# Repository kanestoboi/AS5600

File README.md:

# AS5600

Arduino library for the AS5600 12-bit Magnetic Encoder. This library was written for the [NEMA-17 AS5600 Board](https://github.com/kanestoboi/AS5600-Nema-17-Board).

Features
* Read 12 bit value (0-4095)
* Read angle value in degrees (0-360 degrees)
* Get magnetic strength 
* Get gain

## Example 
The following example reads the angle (0-360) of the magnet relative to the AS5600 encoder in increments of 360/4095
```c
#include <AS5600.h>

AS5600 encoder;
float output;

void setup() {
  Serial.begin(9600);
}

void loop() {
  // get the angle in degrees of the encoder
  output = encoder.getAngle();
  Serial.println(output);
}
````

## More Examples
See [`examples`](https://github.com/kanestoboi/AS5600/tree/master/examples) directory in this repository for more examples including continuous rotation.

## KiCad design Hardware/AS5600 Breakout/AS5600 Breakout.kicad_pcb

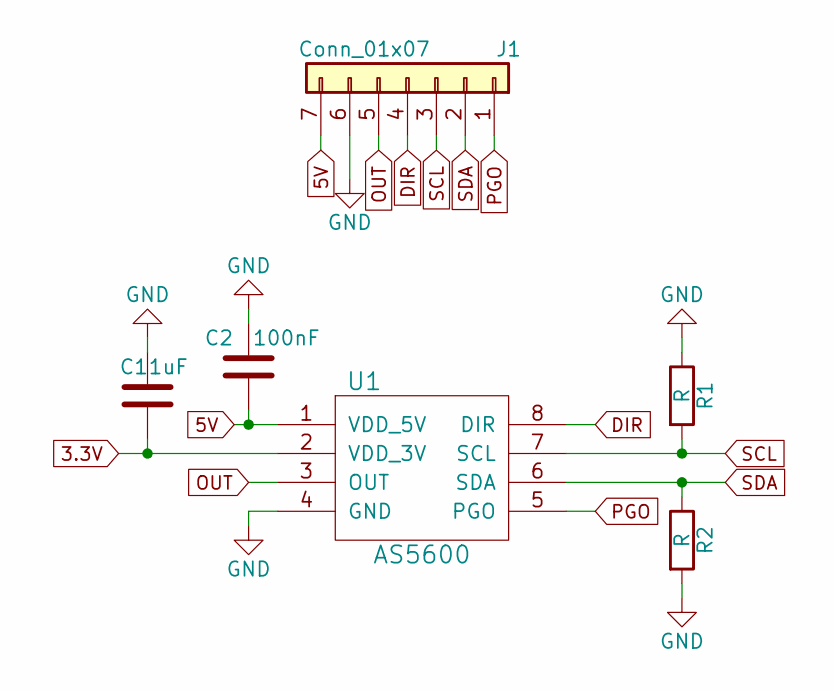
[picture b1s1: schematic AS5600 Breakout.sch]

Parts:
C1: 1uF; C_0805
C2: 100nF; C_0805
J1: Conn_01x07; Pin_Header_Angled_1x07_Pitch2.54mm
R1, R2: R; R_0805
U1: AS5600; SOIC-8-N

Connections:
3.3V: C1.2, U1.2 (VDD_3V)
5V: C2.1, J1.7, U1.1 (VDD_5V)
DIR: J1.4, U1.8 (DIR)
GND: C1.1, C2.2, J1.6, R1.1, R2.2, U1.4 (GND)
OUT: J1.5, U1.3 (OUT)
PGO: J1.1, U1.5 (PGO)
SCL: J1.3, R1.2, U1.7 (SCL)
SDA: J1.2, R2.1, U1.6 (SDA)

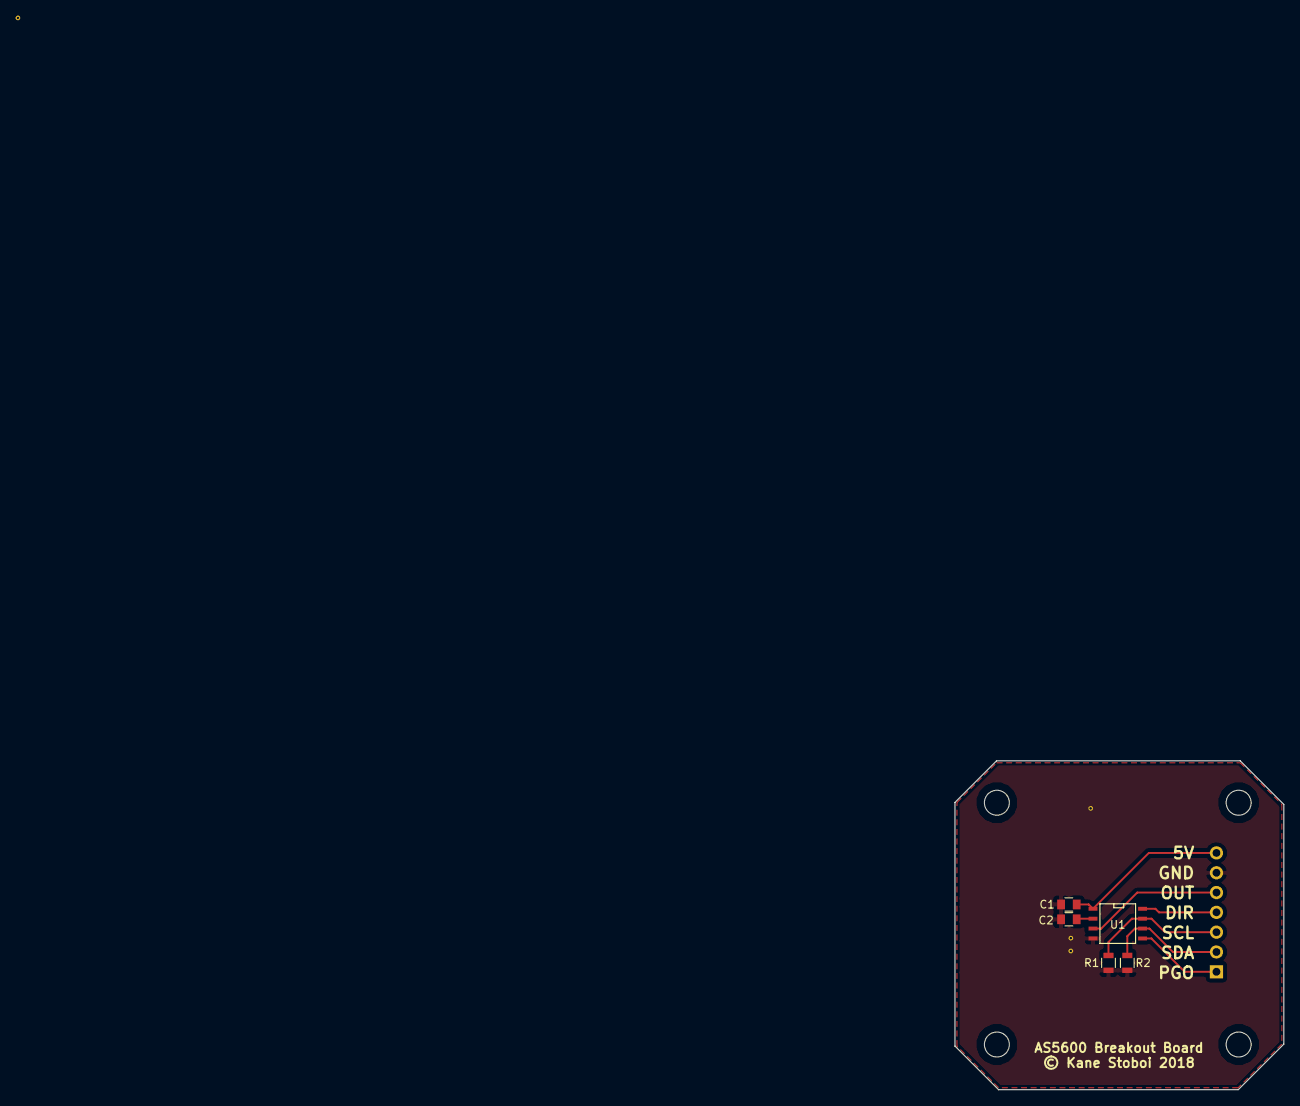
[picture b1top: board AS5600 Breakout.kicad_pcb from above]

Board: 2 copper layers, 42.2 x 42.2 mm, 6 parts (1 on the bottom side), 8 nets.

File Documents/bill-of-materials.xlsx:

ECTE451 Kane Stoboi
 |  |  |  |  |  |  |  |  |  |  | © 2012-2014 Vertex42 LLC
 |  |  |  |  |  | [42] |  |  |  |  | Bill of Materials Template
 | Part Count : | 175
 | Total Cost : | 239.79999999999998
Part # | Part Name | Supplier | Description | Supplier Part Number | Qty | Picture | Unit Cost | Shipping | Cost
 | TMC2100 Breakout | Digikey |  | 1460-1159-ND | 3 |  | 11.32 | 0 | 33.96
 | AS5600-ASOM | Digikey |  | AS5600-ASOMCT-ND | 5 |  | 5.66 |  | 28.3
 | Teensy 3.6 | Digikey |  | 1568-1465-ND | 2 |  | 51.78 |  | 103.56
 | 100nF Capacitor | Digikey |  | 1276-1007-1-ND | 20 |  | 6.4000000000000001E-2 |  | 1.28
 | 10uF Capacitor | Digikey |  | 1276-1096-1-ND | 20 |  | 0.16600000000000001 |  | 3.3200000000000003
 | LED_0603 | Digikey |  | 475-3118-1-ND | 10 |  | 0.437 |  | 4.37
 | Pin Header | Digikey |  | 732-5342-ND | 10 |  | 1.0469999999999999 |  | 10.469999999999999
 | 47k Resistor 0805 | Digikey |  | 311-47.0KCRCT-ND | 100 |  | 2.5600000000000001E-2 |  | 2.56
 | AEAT-6600-T16 | Mouser |  | 630-AEAT-6600-T16 | 3 |  | 11.38 |  | 34.14
 | Circuit Board Manufacture | Elecrow |  | - | 2 |  | 4.9000000000000004 | 8.0399999999999991 | 17.84
 |  |  |  |  |  |  |  |  | 0
 | Total |  |  |  | 175 |  |  |  | 239.79999999999998

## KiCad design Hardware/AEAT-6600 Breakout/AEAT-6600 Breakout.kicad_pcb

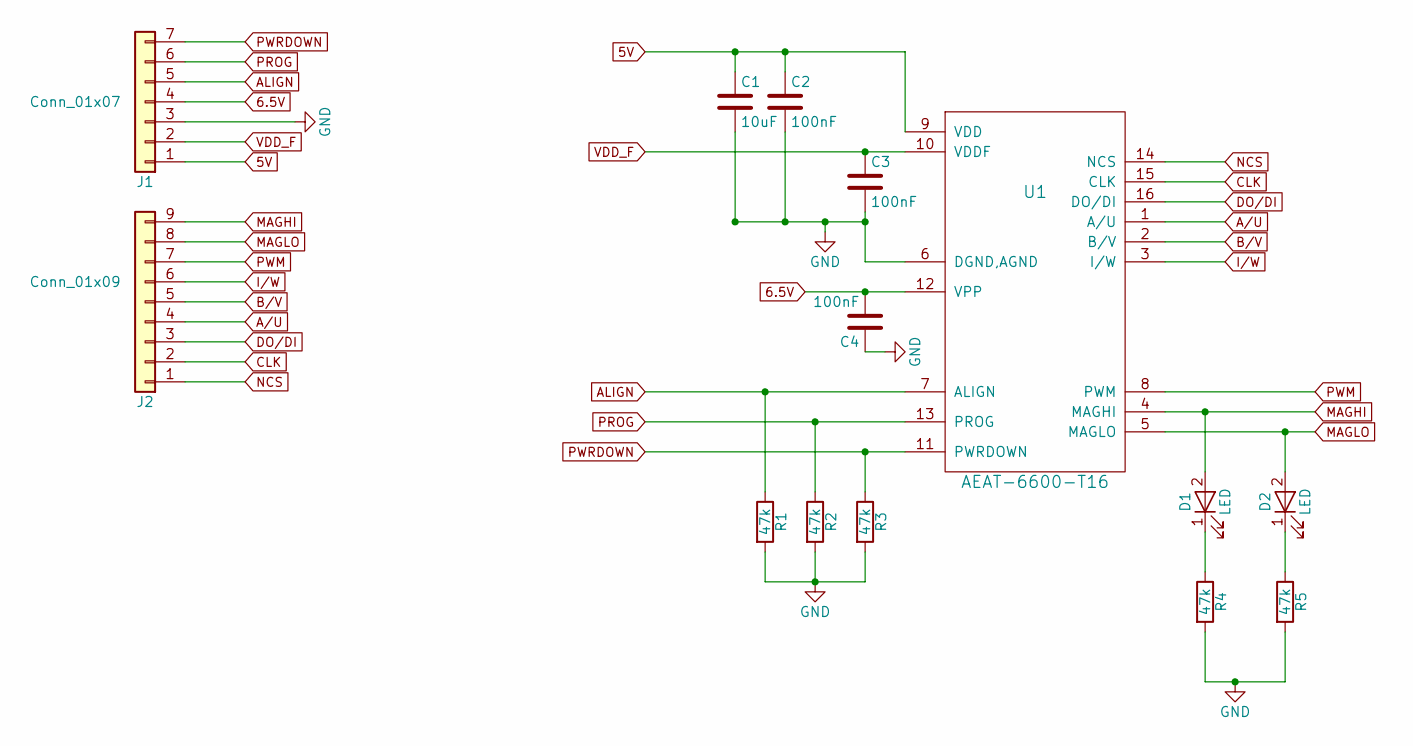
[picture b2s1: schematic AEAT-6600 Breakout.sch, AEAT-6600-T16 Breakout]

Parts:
C1: 10uF; C_0805
C2, C3, C4: 100nF; C_0805
D1, D2: LED; LED_0603
J1: Conn_01x07; Pin_Header_Angled_1x07_Pitch2.54mm
J2: Conn_01x09; Pin_Header_Angled_1x09_Pitch2.54mm
R1, R2, R3, R4, R5: 47k; R_0805
U1: AEAT-6600-T16; TSSOP-16_4.4x5mm_Pitch0.65mm

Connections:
5V: C1.1, C2.1, J1.1, U1.9 (VDD)
6.5V: C4.2, J1.4, U1.12 (VPP)
A/U: J2.4, U1.1 (A/U)
ALIGN: J1.5, R1.1, U1.7 (ALIGN)
B/V: J2.5, U1.2 (B/V)
CLK: J2.2, U1.15 (CLK)
DO/DI: J2.3, U1.16 (DO/DI)
GND: C1.2, C2.2, C3.2, C4.1, J1.3, R1.2, R2.2, R3.2, R4.2, R5.2, U1.6 (DGND,AGND)
I/W: J2.6, U1.3 (I/W)
MAGHI: D1.2 (A), J2.9, U1.4 (MAGHI)
MAGLO: D2.2 (A), J2.8, U1.5 (MAGLO)
NCS: J2.1, U1.14 (NCS)
unnamed: D1.1 (K), R4.1
unnamed: D2.1 (K), R5.1
PROG: J1.6, R2.1, U1.13 (PROG)
PWM: J2.7, U1.8 (PWM)
PWRDOWN: J1.7, R3.1, U1.11 (PWRDOWN)
VDD_F: C3.1, J1.2, U1.10 (VDDF)

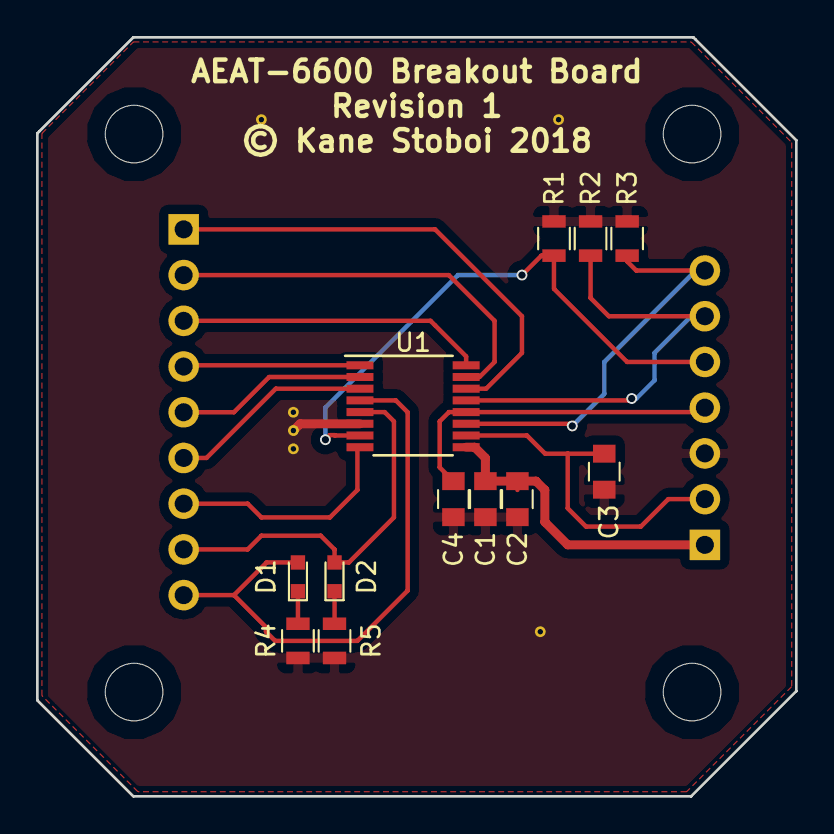
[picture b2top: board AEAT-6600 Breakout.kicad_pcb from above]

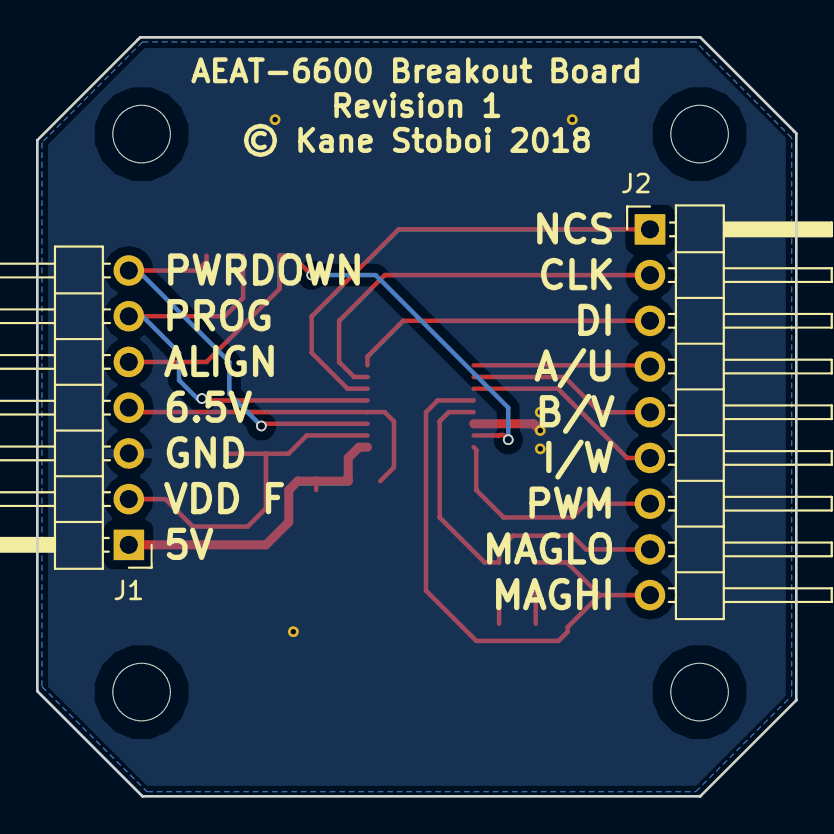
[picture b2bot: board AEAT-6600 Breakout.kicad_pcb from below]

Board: 2 copper layers, 42.2 x 42.2 mm, 14 parts (2 on the bottom side), 18 nets.

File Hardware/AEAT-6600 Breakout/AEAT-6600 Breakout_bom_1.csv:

Component,Description,Part,References,Value,Footprint,Quantity Per PCB,Datasheet,Supplier Part Number,Supplier,Cost Each
1,Unpolarized capacitor,C,C2 C3 C4,100nF,C_0805,3,,1276-1007-1-ND,Digikey,0.064
2,Unpolarized capacitor,C,C1,10uF,C_0805,1,,1276-1096-1-ND,Digikey,0.166
3,LED generic,LED,D1 D2,LED,LED_0603,2,,475-3118-1-ND,Digikey,0.437
4,"Generic connector, single row, 01x07",Conn_01x07,J1,Conn_01x07,Pin_Header_Angled_1x07_Pitch2.54mm,1,,732-5342-ND,Digikey,1.047
5,"Generic connector, single row, 01x09",Conn_01x09,J2,Conn_01x09,Pin_Header_Angled_1x09_Pitch2.54mm,1,,732-5342-ND,Digikey,1.047
6,Resistor,R,R1 R2 R3 R4 R5,47k,R_0805,5,,311-47.0KCRCT-ND,Digikey,0.056
7,,AEAT-6600-T16,U1,AEAT-6600-T16,TSSOP-16_4.4x5mm_Pitch0.65mm,1,,,,





Component Groups:,7
Component Count:,14
Fitted Components:,14
Number of PCBs:,1
Total components:,14
Schematic Version:,1
Schematic Date:,2018-08-18
BoM Date:,19/08/2018 10:19:32 AM
Schematic Source:,C:\Users\kanes\Documents\Projects\ECTE451\Hardware\AEAT-6600 Breakout\AEAT-6600 Breakout.sch
KiCad Version:,Eeschema 4.0.7

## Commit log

2018-08-01 initial commit of report, literature planner and project proposal form
2018-08-07 added brief overview to proposal
2018-08-08 made save
2018-08-08 - Added further to Brief Overview - Added further to Project Description - Added further to Project Plan - Added Further to Resources Required
    - Added TMC2100 Datasheet and application noted
    - Added forms to repo
    - Added endnote library
2018-08-08 added redline
2018-08-11 - added more journals, datasheets and application notes - added redline for project proposal form - added more references to endnote library
2018-08-13 Added more changes to proposal form added BOM Added more references
2018-08-18 Completed Project Proposal
2018-08-18 More journals added
2018-08-18 - Updated BOM - Created AS5600 Breakout schematic and board
2018-08-18 Completed schematic of AEAT-6600 Breakout
2018-08-18 Completed AEAT-6600 Breakout
2018-08-19 Completed breakout boards and BOM
2018-08-22 Created gerbers for pcbs
2018-08-22 Started developing AS5600 library
2018-09-20 - added further to AS5600 arduino library - created model for circuit board holder - finished MATLAB model for AS5600 feedback loop, ready for testing
2018-09-20 - updated filter for MATLAB model - Fixed bug in arduino code causing MSB to be read as LSB and vise versa
2018-09-23 - changed vco to PWM output - Moved encoder into subsystem in simulink model
2018-09-24 - added blank thesis word document
2018-09-24 - removed unnecessary info from abbreviations - removed change history table - added chapter titles
2018-09-26 - modified literature planner
2018-09-26 - added to report introduction and lit review - added reference to endnote
2018-09-29 started implementing contro system in arduino code
2018-09-30 - removed filter as capacitor has been added to 3.3V pin on breakout board - changed drive pin to be using ppm pin
2018-09-30 - added config pins for motor mode control
2018-10-01 - added more documents
2018-10-01 - added more journals to lit review
2018-10-02 - added functions to switch from stealth chop to spread cycle - moved encoder status code to function - moved error calc to function - added enable pin for motor driver - added frequency function to 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
2018-10-03 - added more to lit review
2018-10-03 - added more lit review notes
2018-10-03 - testing spread cycle power
2018-10-03 added more lit review stuff
2018-10-03 more lit review comments
2018-10-07 - added image of stepper motor diagram
2018-10-07 - updated stepper motor schematic
2018-10-07 - added timer interrupt for as5600
2018-10-10 changed read two registers to read one at a time
2018-10-10 moving AS5600 to separate repo
2018-10-10 - added keywords file - added AS5600.ino file - changed private variables and functions to have _ prefix
2018-10-10 updated keywords with function names
2018-10-10 moved example into examples folder
2018-10-10 changed example name to readAngle
2018-10-10 moved example to readAngle folder
2018-10-11 - moving AS5600 into separate repo
2018-10-11 - added basic data collected for position and velocity
2018-10-11 - added more position data for stealth and spreadcycle at 200Hz
2018-10-11 added image of AS5600 breakout board
2018-10-11 adding subtree
2018-10-11 adding readMagnet example
2019-02-09 added continuous rotation example code
2019-02-09 added functionality to readAngle example
2019-04-02 many bug fixes:
    * _getRegister2 broken, fixed with call to _getRegister twice
    * _getRegister broken, fixed with adding extra parameter to `requestFrom`
    * changed types to explicit bit lenght (e.g. `uint16_t`)
    * added `isMagnet...` functions for convenience
    * added `getScaledAngle` for easy conversion to degrees (0 to 360)
    * took out buggy mamber variables `_msb` and `_lsb` variables
2021-02-05 Added function descriptions and minor refactoring
2021-02-08 Create README.md
    Added readme
2021-02-08 Update README.md
    updated syntax highlighting
2021-02-08 Update README.md
    amended typo
2021-02-16 Added functionality to set configuration registers
2022-02-19 Fixed bits for reading magnet ststus

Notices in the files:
Hardware/AEAT-6600 Breakout/AEAT-6600 Breakout.kicad_pcb:
© Kane Stoboi 2018
